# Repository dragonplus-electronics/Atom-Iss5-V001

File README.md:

# Atom Iss5 Repro V001 (Near Replica)
 This board is intended to be used as a replica Issue 5 board for the Acorn Atom. If you build it, please share your experiences via Stardot or other Acorn Atom online forums.

 ## KiCad File Content
 
 Wherever possible, custom symbols have been created in order to align closely to the structure of the original Atom schematics. The schematic itself though has been split into logical areas with off-sheet address and data busses as well as global pin assignments. When you open the project, you will likely need to 'Rescue' the symbols, as you will not have the custom libraries.
 
 The PCB files themselves are not included in this repository, purely because at this stage I do not want people running off and creating all sorts of forks and modified boards. Please do not ask me for them, as refusal often offends. :) Those files will follow once all Atom repro work is concluded.
 
 Although the PCB is close to identical in most respects, including the aesthetics of the silkscreen etc, certain elements have been changed in order to facilitate sourcing/placement of certain components. These are listed below:
 
 ## Footprint Changes
   - Links 1-3 & 6-7 have been modified so that they are joined using a 2.54mm pitch header, instead of non-standard length links of wire.
   
   - SK1 - the power socket has been switched for a modern footprint. Suitable sockets are the Cliff FC681465 or the FC681478. The former will accept both 2.1mm and 2.5mm barrel jacks, whilst the latter will only accept 2.1mm barrel jacks.
   
   - SK2 - this has been swapped for a modern DIN-7 socket footprint. These are readily available. One such example is: https://uk.farnell.com/pro-signal/psg03465/din-socket-pcb-7p/dp/1791759

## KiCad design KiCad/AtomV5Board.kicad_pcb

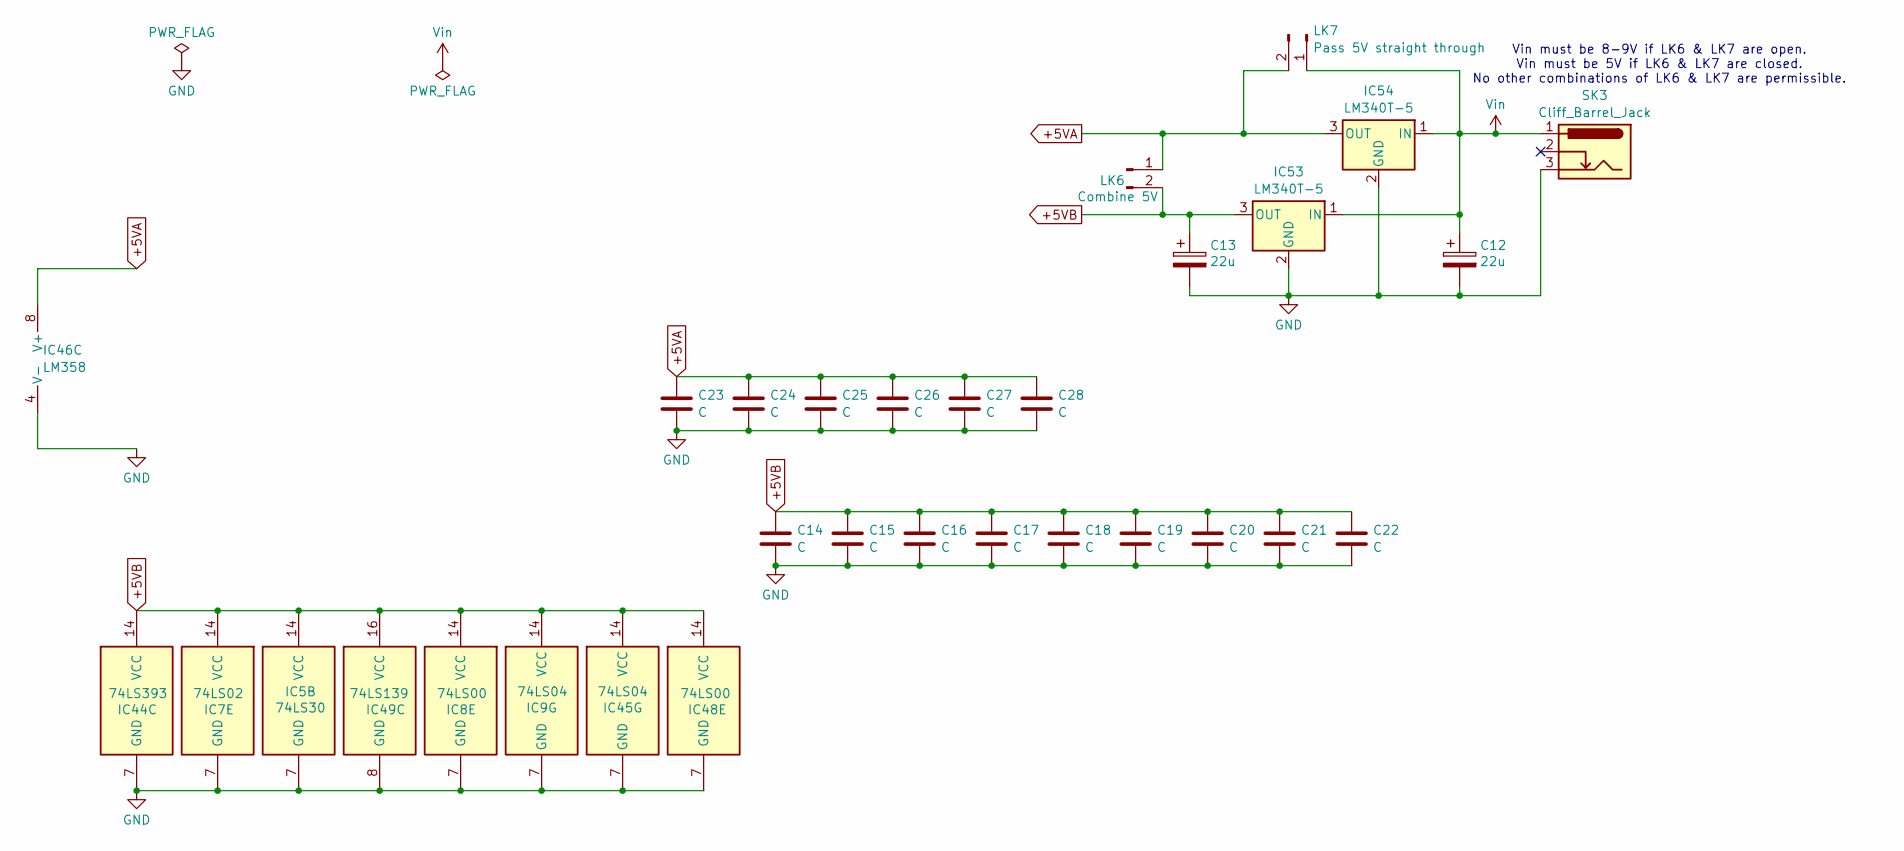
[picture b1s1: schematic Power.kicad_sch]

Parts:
C12: 22u; CP_Axial_LineOnly_P17.78mm_Horizontal
C13: 22u; CP_Axial_LineOnly_P19.05mm_Horizontal
C14, C15, C16, C17, C18, C19, C20, C21, C22, C23, C24, C25, C26, C27, C28: C; C_Disc_LineOnly_P5.08mm
IC5: 74LS30; DIP-14_W7.62mm_InnerMarking
IC7: 74LS02; DIP-14_W7.62mm_InnerMarking
IC8, IC48: 74LS00; DIP-14_W7.62mm_InnerMarking
IC9, IC45: 74LS04; DIP-14_W7.62mm_InnerMarking
IC44: 74LS393; DIP-14_W7.62mm_InnerMarking
IC46: LM358; DIP-8_W7.62mm_InnerMarking
IC49: 74LS139; DIP-16_W7.62mm_InnerMarking
IC53, IC54: LM340T-5; TO-220-3_Horizontal_TabDown
LK6: Combine 5V; PinHeader_1x02_P2.54mm_Vertical
LK7: Pass 5V straight through; PinHeader_1x02_P2.54mm_Vertical
SK3: Cliff_Barrel_Jack; Cliff_FC681461_Barrel_Jack

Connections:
+5VA: C23.1, C24.1, C25.1, C26.1, C27.1, C28.1, IC46.8 (V+), IC54.3 (OUT), LK6.1, LK7.2; also elsewhere on the board
+5VB: C13.1, C14.1, C15.1, C16.1, C17.1, C18.1, C19.1, C20.1, C21.1, C22.1, IC5.14 (VCC), IC7.14 (VCC), IC8.14 (VCC), IC9.14 (VCC), IC44.14 (VCC), IC45.14 (VCC), IC48.14 (VCC), IC49.16 (VCC), IC53.3 (OUT), LK6.2; also elsewhere on the board
GND: C12.2, C13.2, C14.2, C15.2, C16.2, C17.2, C18.2, C19.2, C20.2, C21.2, C22.2, C23.2, C24.2, C25.2, C26.2, C27.2, C28.2, IC5.7 (GND), IC7.7 (GND), IC8.7 (GND), IC9.7 (GND), IC44.7 (GND), IC45.7 (GND), IC46.4 (V-), IC48.7 (GND), IC49.8 (GND), IC53.2 (GND), IC54.2 (GND), SK3.3; also elsewhere on the board
Vin: C12.1, IC53.1 (IN), IC54.1 (IN), LK7.1, SK3.1

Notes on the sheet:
Vin must be 8-9V if LK6 & LK7 are open. Vin must be 5V if LK6 & LK7 are closed. No other combinations of LK6 & LK7 are permissible.

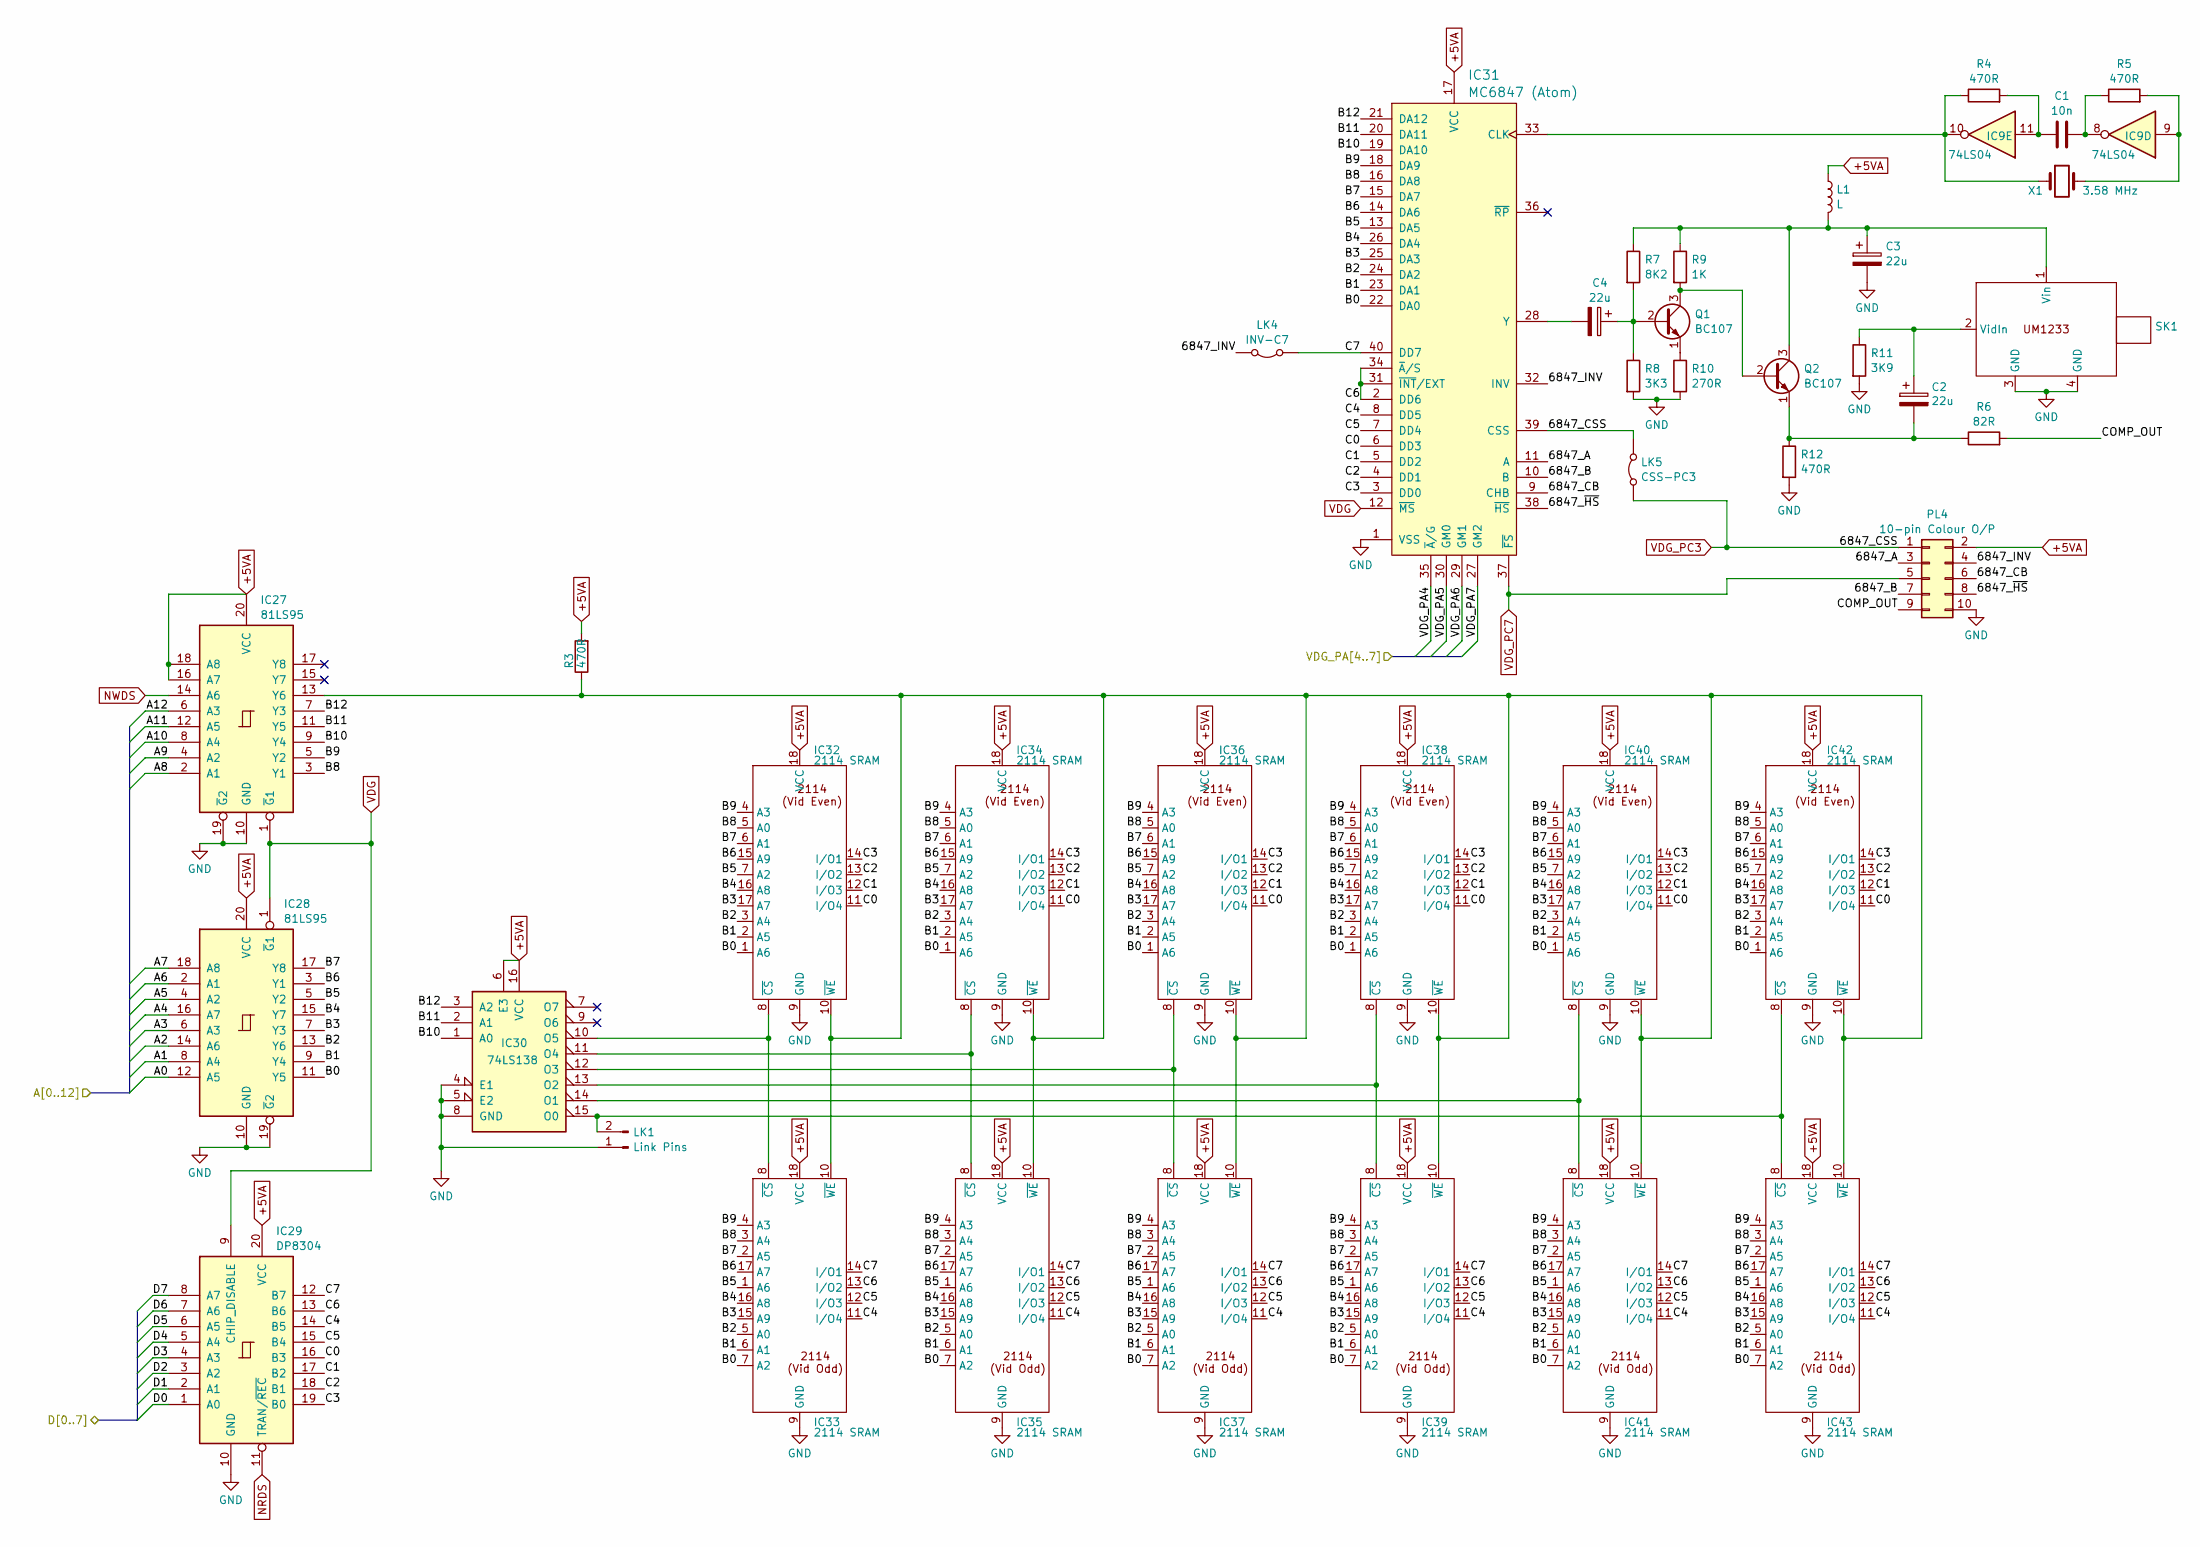
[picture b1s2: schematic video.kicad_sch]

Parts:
C1: 10n; C_Disc_LineOnly_P10.16mm
C2, C3: 22u; CP_Axial_LineOnly_P17.78mm_Horizontal
C4: 22u; CP_Axial_LineOnly_P15.24mm_Horizontal
IC9: 74LS04; DIP-14_W7.62mm_InnerMarking
IC27, IC28: 81LS95; DIP-20_W7.62mm_InnerMarking
IC29: DP8304; DIP-20_W7.62mm_InnerMarking
IC30: 74LS138; DIP-16_W7.62mm_InnerMarking
IC31: MC6847 (Atom); DIP-40_W15.24mm_InnerMarking
IC32, IC33, IC34, IC35, IC36, IC37, IC38, IC39, IC40, IC41, IC42, IC43: 2114 SRAM; DIP-18_W7.62mm_InnerMarking
L1: L; L_Axial_L7.0mm_D3.3mm_P5.08mm_Vertical_Fastron_MICC
LK1: Link Pins; PinHeader_1x02_P2.54mm_Vertical
LK4: INV-C7; SolderJumper-2_P1.3mm_Bridged_Pad1.0x1.5mm
LK5: CSS-PC3; SolderJumper-2_P1.3mm_Bridged_Pad1.0x1.5mm
PL4: 10-pin Colour O/P; PinHeader_2x05_P2.54mm_Vertical
Q1, Q2: BC107; TO-18-3_WidePinout
R3, R5: 470R; R_Axial_DIN0207_LineOnly_P2.54mm_Vertical
R4, R12: 470R; R_Axial_DIN0207_LineOnly_P10.16mm_Horizontal
R6: 82R; R_Axial_DIN0207_LineOnly_P10.16mm_Horizontal
R7: 8K2; R_Axial_DIN0207_LineOnly_P10.16mm_Horizontal
R8: 3K3; R_Axial_DIN0207_LineOnly_P10.16mm_Horizontal
R9: 1K; R_Axial_DIN0207_LineOnly_P10.16mm_Horizontal
R10: 270R; R_Axial_DIN0207_LineOnly_P10.16mm_Horizontal
R11: 3K9; R_Axial_DIN0207_LineOnly_P10.16mm_Horizontal
SK1: UM1233
X1: 3.58 MHz; C_Disc_LineOnly_P10.16mm

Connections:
+5VA: IC27.16 (A7), IC27.18 (A8), IC27.20 (VCC), IC28.20 (VCC), IC29.20 (VCC), IC30.6 (E3), IC30.16 (VCC), IC31.17 (VCC), IC32.18 (VCC), IC33.18 (VCC), IC34.18 (VCC), IC35.18 (VCC), IC36.18 (VCC), IC37.18 (VCC), IC38.18 (VCC), IC39.18 (VCC), IC40.18 (VCC), IC41.18 (VCC), IC42.18 (VCC), IC43.18 (VCC), L1.1, PL4.2, R3.2; also elsewhere on the board
/6522_PIA & Ports/A0: IC28.12 (A5); also elsewhere on the board
/6522_PIA & Ports/A1: IC28.8 (A4); also elsewhere on the board
/6522_PIA & Ports/A2: IC28.14 (A6); also elsewhere on the board
/6522_PIA & Ports/A3: IC28.6 (A3); also elsewhere on the board
/6522_PIA & Ports/A4: IC28.16 (A7); also elsewhere on the board
/6522_PIA & Ports/A5: IC28.4 (A2); also elsewhere on the board
/6522_PIA & Ports/A6: IC28.2 (A1); also elsewhere on the board
/6522_PIA & Ports/A7: IC28.18 (A8); also elsewhere on the board
/6522_PIA & Ports/A8: IC27.2 (A1); also elsewhere on the board
/6522_PIA & Ports/A9: IC27.4 (A2); also elsewhere on the board
/6522_PIA & Ports/A10: IC27.8 (A4); also elsewhere on the board
/6522_PIA & Ports/A11: IC27.12 (A5); also elsewhere on the board
/6522_PIA & Ports/A12: IC27.6 (A3); also elsewhere on the board
/6522_PIA & Ports/D0: IC29.1 (A0); also elsewhere on the board
/6522_PIA & Ports/D1: IC29.2 (A1); also elsewhere on the board
/6522_PIA & Ports/D2: IC29.3 (A2); also elsewhere on the board
/6522_PIA & Ports/D3: IC29.4 (A3); also elsewhere on the board
/6522_PIA & Ports/D4: IC29.5 (A4); also elsewhere on the board
/6522_PIA & Ports/D5: IC29.6 (A5); also elsewhere on the board
/6522_PIA & Ports/D6: IC29.7 (A6); also elsewhere on the board
/6522_PIA & Ports/D7: IC29.8 (A7); also elsewhere on the board
/CPU, ROMs & 8255 PIA/VDG_PA4: IC31.35 (~A/G); also elsewhere on the board
/CPU, ROMs & 8255 PIA/VDG_PA5: IC31.30 (GM0); also elsewhere on the board
/CPU, ROMs & 8255 PIA/VDG_PA6: IC31.29 (GM1); also elsewhere on the board
/CPU, ROMs & 8255 PIA/VDG_PA7: IC31.27 (GM2); also elsewhere on the board
/Video/6847_A: IC31.11 (A), PL4.3
/Video/6847_B: IC31.10 (B), PL4.7
/Video/6847_CB: IC31.9 (CHB), PL4.6
/Video/6847_INV: IC31.32 (INV), LK4.2 (B), PL4.4
/Video/6847_~HS: IC31.38 (~HS), PL4.8
/Video/B0: IC28.11 (Y5), IC31.22 (DA0), IC32.1 (A6), IC33.7 (A2), IC34.1 (A6), IC35.7 (A2), IC36.1 (A6), IC37.7 (A2), IC38.1 (A6), IC39.7 (A2), IC40.1 (A6), IC41.7 (A2), IC42.1 (A6), IC43.7 (A2)
/Video/B1: IC28.9 (Y4), IC31.23 (DA1), IC32.2 (A5), IC33.6 (A1), IC34.2 (A5), IC35.6 (A1), IC36.2 (A5), IC37.6 (A1), IC38.2 (A5), IC39.6 (A1), IC40.2 (A5), IC41.6 (A1), IC42.2 (A5), IC43.6 (A1)
/Video/B2: IC28.13 (Y6), IC31.24 (DA2), IC32.3 (A4), IC33.5 (A0), IC34.3 (A4), IC35.5 (A0), IC36.3 (A4), IC37.5 (A0), IC38.3 (A4), IC39.5 (A0), IC40.3 (A4), IC41.5 (A0), IC42.3 (A4), IC43.5 (A0)
/Video/B3: IC28.7 (Y3), IC31.25 (DA3), IC32.17 (A7), IC33.15 (A9), IC34.17 (A7), IC35.15 (A9), IC36.17 (A7), IC37.15 (A9), IC38.17 (A7), IC39.15 (A9), IC40.17 (A7), IC41.15 (A9), IC42.17 (A7), IC43.15 (A9)
/Video/B4: IC28.15 (Y7), IC31.26 (DA4), IC32.16 (A8), IC33.16 (A8), IC34.16 (A8), IC35.16 (A8), IC36.16 (A8), IC37.16 (A8), IC38.16 (A8), IC39.16 (A8), IC40.16 (A8), IC41.16 (A8), IC42.16 (A8), IC43.16 (A8)
/Video/B5: IC28.5 (Y2), IC31.13 (DA5), IC32.7 (A2), IC33.1 (A6), IC34.7 (A2), IC35.1 (A6), IC36.7 (A2), IC37.1 (A6), IC38.7 (A2), IC39.1 (A6), IC40.7 (A2), IC41.1 (A6), IC42.7 (A2), IC43.1 (A6)
/Video/B6: IC28.3 (Y1), IC31.14 (DA6), IC32.15 (A9), IC33.17 (A7), IC34.15 (A9), IC35.17 (A7), IC36.15 (A9), IC37.17 (A7), IC38.15 (A9), IC39.17 (A7), IC40.15 (A9), IC41.17 (A7), IC42.15 (A9), IC43.17 (A7)
/Video/B7: IC28.17 (Y8), IC31.15 (DA7), IC32.6 (A1), IC33.2 (A5), IC34.6 (A1), IC35.2 (A5), IC36.6 (A1), IC37.2 (A5), IC38.6 (A1), IC39.2 (A5), IC40.6 (A1), IC41.2 (A5), IC42.6 (A1), IC43.2 (A5)
/Video/B8: IC27.3 (Y1), IC31.16 (DA8), IC32.5 (A0), IC33.3 (A4), IC34.5 (A0), IC35.3 (A4), IC36.5 (A0), IC37.3 (A4), IC38.5 (A0), IC39.3 (A4), IC40.5 (A0), IC41.3 (A4), IC42.5 (A0), IC43.3 (A4)
/Video/B9: IC27.5 (Y2), IC31.18 (DA9), IC32.4 (A3), IC33.4 (A3), IC34.4 (A3), IC35.4 (A3), IC36.4 (A3), IC37.4 (A3), IC38.4 (A3), IC39.4 (A3), IC40.4 (A3), IC41.4 (A3), IC42.4 (A3), IC43.4 (A3)
/Video/B10: IC27.9 (Y4), IC30.1 (A0), IC31.19 (DA10)
/Video/B11: IC27.11 (Y5), IC30.2 (A1), IC31.20 (DA11)
/Video/B12: IC27.7 (Y3), IC30.3 (A2), IC31.21 (DA12)
/Video/C0: IC29.16 (B3), IC31.6 (DD3), IC32.11 (I/O4), IC34.11 (I/O4), IC36.11 (I/O4), IC38.11 (I/O4), IC40.11 (I/O4), IC42.11 (I/O4)
/Video/C1: IC29.17 (B2), IC31.5 (DD2), IC32.12 (I/O3), IC34.12 (I/O3), IC36.12 (I/O3), IC38.12 (I/O3), IC40.12 (I/O3), IC42.12 (I/O3)
/Video/C2: IC29.18 (B1), IC31.4 (DD1), IC32.13 (I/O2), IC34.13 (I/O2), IC36.13 (I/O2), IC38.13 (I/O2), IC40.13 (I/O2), IC42.13 (I/O2)
/Video/C3: IC29.19 (B0), IC31.3 (DD0), IC32.14 (I/O1), IC34.14 (I/O1), IC36.14 (I/O1), IC38.14 (I/O1), IC40.14 (I/O1), IC42.14 (I/O1)
/Video/C4: IC29.14 (B5), IC31.8 (DD5), IC33.11 (I/O4), IC35.11 (I/O4), IC37.11 (I/O4), IC39.11 (I/O4), IC41.11 (I/O4), IC43.11 (I/O4)
/Video/C5: IC29.15 (B4), IC31.7 (DD4), IC33.12 (I/O3), IC35.12 (I/O3), IC37.12 (I/O3), IC39.12 (I/O3), IC41.12 (I/O3), IC43.12 (I/O3)
/Video/C6: IC29.13 (B6), IC31.2 (DD6), IC31.31 (~INT/EXT), IC31.34 (~A/S), IC33.13 (I/O2), IC35.13 (I/O2), IC37.13 (I/O2), IC39.13 (I/O2), IC41.13 (I/O2), IC43.13 (I/O2)
/Video/C7: IC29.12 (B7), IC31.40 (DD7), IC33.14 (I/O1), IC35.14 (I/O1), IC37.14 (I/O1), IC39.14 (I/O1), IC41.14 (I/O1), IC43.14 (I/O1), LK4.1 (A)
/Video/COMP_OUT: PL4.9, R6.2
GND: C3.2, IC27.10 (GND), IC27.19 (~G2), IC28.10 (GND), IC28.19 (~G2), IC29.10 (GND), IC30.4 (E1), IC30.5 (E2), IC30.8 (GND), IC31.1 (VSS), IC32.9 (GND), IC33.9 (GND), IC34.9 (GND), IC35.9 (GND), IC36.9 (GND), IC37.9 (GND), IC38.9 (GND), IC39.9 (GND), IC40.9 (GND), IC41.9 (GND), IC42.9 (GND), IC43.9 (GND), LK1.1, PL4.10, R8.2, R10.2, R11.2, R12.2, SK1.3 (GND), SK1.4 (GND); also elsewhere on the board
NRDS: IC29.11 (TRAN/~REC); also elsewhere on the board
NWDS: IC27.14 (A6); also elsewhere on the board
unnamed: C1.1, IC9.11, R4.2
unnamed: C1.2, IC9.8, R5.1
unnamed: IC9.9, R5.2, X1.2
unnamed: IC27.13 (Y6), IC32.10 (~WE), IC33.10 (~WE), IC34.10 (~WE), IC35.10 (~WE), IC36.10 (~WE), IC37.10 (~WE), IC38.10 (~WE), IC39.10 (~WE), IC40.10 (~WE), IC41.10 (~WE), IC42.10 (~WE), IC43.10 (~WE), R3.1
unnamed: IC30.15 (O0), IC42.8 (~CS), IC43.8 (~CS), LK1.2
unnamed: IC30.14 (O1), IC40.8 (~CS), IC41.8 (~CS)
unnamed: IC30.13 (O2), IC38.8 (~CS), IC39.8 (~CS)
unnamed: IC30.12 (O3), IC36.8 (~CS), IC37.8 (~CS)
unnamed: IC30.11 (O4), IC34.8 (~CS), IC35.8 (~CS)
unnamed: IC30.10 (O5), IC32.8 (~CS), IC33.8 (~CS)
unnamed: IC9.10, IC31.33 (CLK), R4.1, X1.1
unnamed: C4.2, IC31.28 (Y)
unnamed: C4.1, Q1.2 (B), R7.2, R8.1
unnamed: Q1.3 (C), Q2.2 (B), R9.2
unnamed: Q1.1 (E), R10.1
unnamed: C3.1, L1.2, Q2.3 (C), R7.1, R9.1, SK1.1 (Vin)
unnamed: C2.2, Q2.1 (E), R6.1, R12.1
unnamed: C2.1, R11.1, SK1.2 (VidIn)
VDG: IC27.1 (~G1), IC28.1 (~G1), IC29.9 (CHIP_DISABLE), IC31.12 (~MS); also elsewhere on the board
VDG_PC3: IC31.39 (CSS), LK5.1 (A), LK5.2 (B), PL4.1; also elsewhere on the board
VDG_PC7: IC31.37 (~FS), PL4.5; also elsewhere on the board

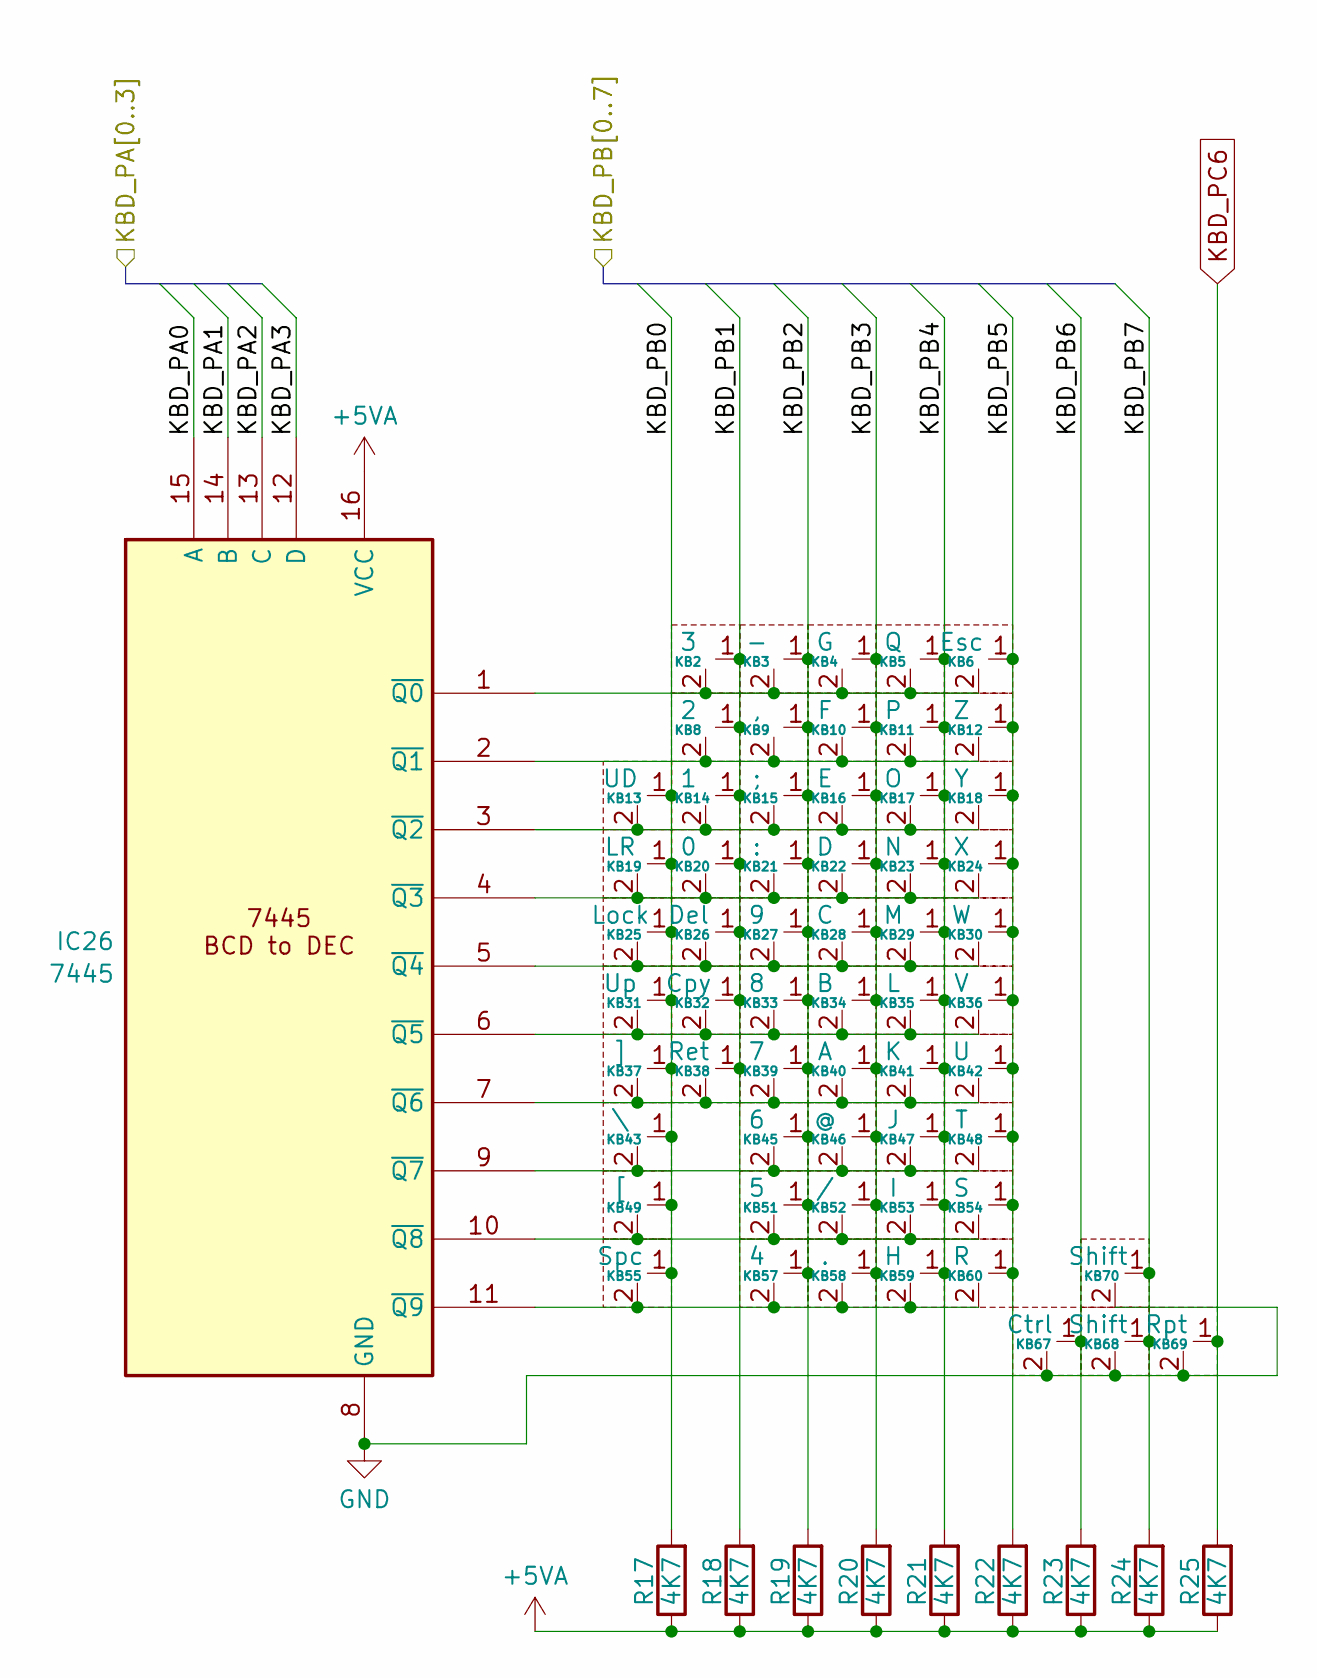
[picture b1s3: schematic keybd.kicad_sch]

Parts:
IC26: 7445; DIP-16_W7.62mm_InnerMarking
KB2: 3; AtomKeyswitch
KB3: -; AtomKeyswitch
KB4: G; AtomKeyswitch
KB5: Q; AtomKeyswitch
KB6: Esc; AtomKeyswitch
KB8: 2; AtomKeyswitch
KB9: ,; AtomKeyswitch
KB10: F; AtomKeyswitch
KB11: P; AtomKeyswitch
KB12: Z; AtomKeyswitch
KB13: UD; AtomKeyswitch
KB14: 1; AtomKeyswitch
KB15: ;; AtomKeyswitch
KB16: E; AtomKeyswitch
KB17: O; AtomKeyswitch
KB18: Y; AtomKeyswitch
KB19: LR; AtomKeyswitch
KB20: 0; AtomKeyswitch
KB21: :; AtomKeyswitch
KB22: D; AtomKeyswitch
KB23: N; AtomKeyswitch
KB24: X; AtomKeyswitch
KB25: Lock; AtomKeyswitch
KB26: Del; AtomKeyswitch
KB27: 9; AtomKeyswitch
KB28: C; AtomKeyswitch
KB29: M; AtomKeyswitch
KB30: W; AtomKeyswitch
KB31: Up; AtomKeyswitch
KB32: Cpy; AtomKeyswitch
KB33: 8; AtomKeyswitch
KB34: B; AtomKeyswitch
KB35: L; AtomKeyswitch
KB36: V; AtomKeyswitch
KB37: ]; AtomKeyswitch
KB38: Ret; AtomKeyswitch
KB39: 7; AtomKeyswitch
KB40: A; AtomKeyswitch
KB41: K; AtomKeyswitch
KB42: U; AtomKeyswitch
KB43: \; AtomKeyswitch
KB45: 6; AtomKeyswitch
KB46: @; AtomKeyswitch
KB47: J; AtomKeyswitch
KB48: T; AtomKeyswitch
KB49: [; AtomKeyswitch
KB51: 5; AtomKeyswitch
KB52: /; AtomKeyswitch
KB53: I; AtomKeyswitch
KB54: S; AtomKeyswitch
KB55: Spc; AtomKeyswitch
KB57: 4; AtomKeyswitch
KB58: .; AtomKeyswitch
KB59: H; AtomKeyswitch
KB60: R; AtomKeyswitch
KB67: Ctrl; AtomKeyswitch
KB68, KB70: Shift; AtomKeyswitch
KB69: Rpt; AtomKeyswitch
R17, R18: 4K7; R_Axial_DIN0207_LineOnly_P5.08mm_Vertical
R19, R25: 4K7; R_Axial_DIN0207_LineOnly_P4.00mm_Vertical
R20, R21, R22, R23, R24: 4K7; R_Axial_DIN0207_LineOnly_P2.54mm_Vertical

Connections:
+5VA: IC26.16 (VCC), R17.1, R18.1, R19.1, R20.1, R21.1, R22.1, R23.1, R24.1, R25.1; also elsewhere on the board
/CPU, ROMs & 8255 PIA/KBD_PA0: IC26.15 (A); also elsewhere on the board
/CPU, ROMs & 8255 PIA/KBD_PA1: IC26.14 (B); also elsewhere on the board
/CPU, ROMs & 8255 PIA/KBD_PA2: IC26.13 (C); also elsewhere on the board
/CPU, ROMs & 8255 PIA/KBD_PA3: IC26.12 (D); also elsewhere on the board
/CPU, ROMs & 8255 PIA/KBD_PB0: KB13.1, KB19.1, KB25.1, KB31.1, KB37.1, KB43.1, KB49.1, KB55.1, R17.2; also elsewhere on the board
/CPU, ROMs & 8255 PIA/KBD_PB1: KB2.1, KB8.1, KB14.1, KB20.1, KB26.1, KB32.1, KB38.1, R18.2; also elsewhere on the board
/CPU, ROMs & 8255 PIA/KBD_PB2: KB3.1, KB9.1, KB15.1, KB21.1, KB27.1, KB33.1, KB39.1, KB45.1, KB51.1, KB57.1, R19.2; also elsewhere on the board
/CPU, ROMs & 8255 PIA/KBD_PB3: KB4.1, KB10.1, KB16.1, KB22.1, KB28.1, KB34.1, KB40.1, KB46.1, KB52.1, KB58.1, R20.2; also elsewhere on the board
/CPU, ROMs & 8255 PIA/KBD_PB4: KB5.1, KB11.1, KB17.1, KB23.1, KB29.1, KB35.1, KB41.1, KB47.1, KB53.1, KB59.1, R21.2; also elsewhere on the board
/CPU, ROMs & 8255 PIA/KBD_PB5: KB6.1, KB12.1, KB18.1, KB24.1, KB30.1, KB36.1, KB42.1, KB48.1, KB54.1, KB60.1, R22.2; also elsewhere on the board
/CPU, ROMs & 8255 PIA/KBD_PB6: KB67.1, R23.2; also elsewhere on the board
/CPU, ROMs & 8255 PIA/KBD_PB7: KB68.1, KB70.1, R24.2; also elsewhere on the board
GND: IC26.8 (GND), KB67.2, KB68.2, KB69.2, KB70.2; also elsewhere on the board
KBD_PC6: KB69.1, R25.2; also elsewhere on the board
unnamed: IC26.1 (~Q0), KB2.2, KB3.2, KB4.2, KB5.2, KB6.2
unnamed: IC26.2 (~Q1), KB8.2, KB9.2, KB10.2, KB11.2, KB12.2
unnamed: IC26.3 (~Q2), KB13.2, KB14.2, KB15.2, KB16.2, KB17.2, KB18.2
unnamed: IC26.4 (~Q3), KB19.2, KB20.2, KB21.2, KB22.2, KB23.2, KB24.2
unnamed: IC26.5 (~Q4), KB25.2, KB26.2, KB27.2, KB28.2, KB29.2, KB30.2
unnamed: IC26.6 (~Q5), KB31.2, KB32.2, KB33.2, KB34.2, KB35.2, KB36.2
unnamed: IC26.7 (~Q6), KB37.2, KB38.2, KB39.2, KB40.2, KB41.2, KB42.2
unnamed: IC26.9 (~Q7), KB43.2, KB45.2, KB46.2, KB47.2, KB48.2
unnamed: IC26.10 (~Q8), KB49.2, KB51.2, KB52.2, KB53.2, KB54.2
unnamed: IC26.11 (~Q9), KB55.2, KB57.2, KB58.2, KB59.2, KB60.2
